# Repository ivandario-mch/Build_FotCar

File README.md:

# Build_FotCar
Construcción del carrito

Carpetas:

Robotica 
--+
  |
  |
  +--CodigosArduino
  |
  |
  |
  +-- Hullas Circuitos
  |
  |
  |
  |
  +-- Diseños 3D

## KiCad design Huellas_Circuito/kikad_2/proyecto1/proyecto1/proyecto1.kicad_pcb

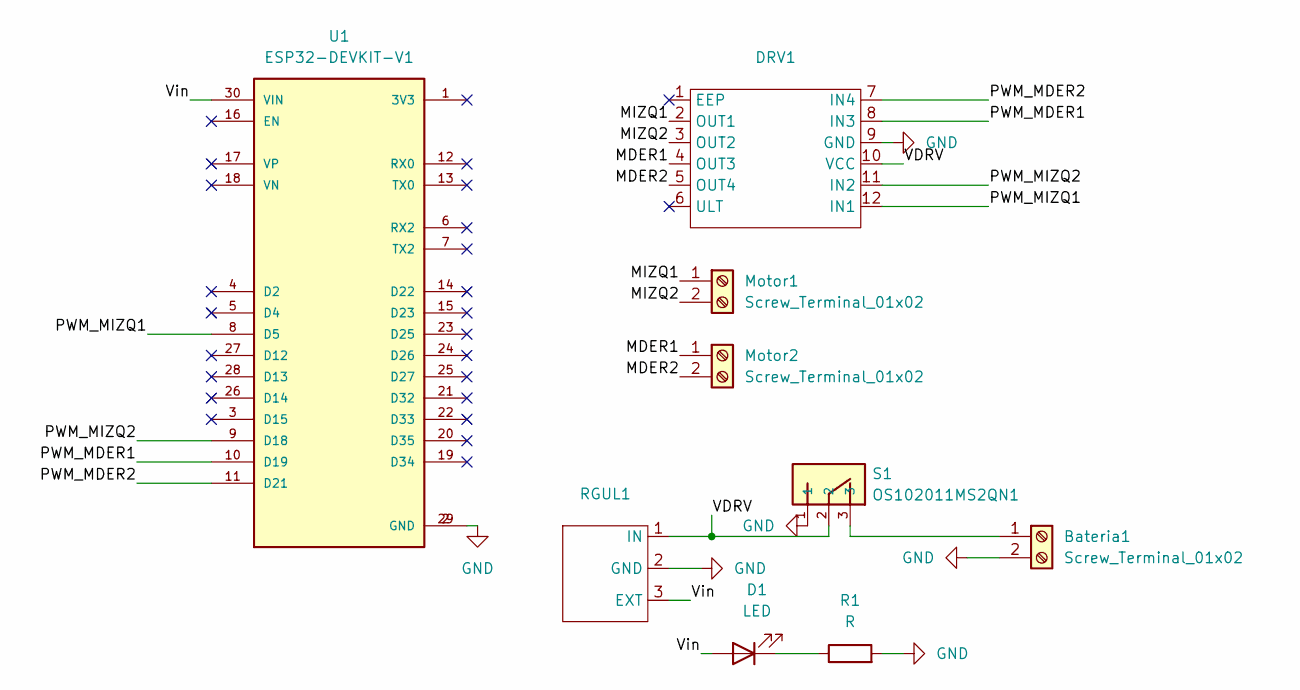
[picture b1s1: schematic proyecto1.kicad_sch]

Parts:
Bateria1: Screw_Terminal_01x02; Molex_KK-254_AE-6410-02A_1x02_P2.54mm_Vertical
D1: LED; LED_D3.0mm
DRV1: DRV_8833
Motor1, Motor2: Screw_Terminal_01x02; Molex_KK-254_AE-6410-02A_1x02_P2.54mm_Vertical
R1: R; R_Axial_DIN0207_L6.3mm_D2.5mm_P7.62mm_Horizontal
RGUL1: RGUL1
S1: OS102011MS2QN1; SW_OS102011MS2QN1
U1: ESP32-DEVKIT-V1; MODULE_ESP32_DEVKIT_V1; PARTREV N/A

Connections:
/MDER1: DRV1.4 (OUT3), Motor2.1
/MDER2: DRV1.5 (OUT4), Motor2.2
/MIZQ1: DRV1.2 (OUT1), Motor1.1
/MIZQ2: DRV1.3 (OUT2), Motor1.2
/PWM_MDER1: DRV1.8 (IN3), U1.10 (D19)
/PWM_MDER2: DRV1.7 (IN4), U1.11 (D21)
/PWM_MIZQ1: DRV1.12 (IN1), U1.8 (D5)
/PWM_MIZQ2: DRV1.11 (IN2), U1.9 (D18)
/VDRV: DRV1.10 (VCC), RGUL1.1 (IN), S1.2
/Vin: D1.2 (A), RGUL1.3 (EXT), U1.30 (VIN)
GND: Bateria1.2, DRV1.9 (GND), R1.2, RGUL1.2 (GND), S1.1, U1.2 (GND), U1.29 (GND)
unnamed: Bateria1.1, S1.3
unnamed: D1.1 (K), R1.1

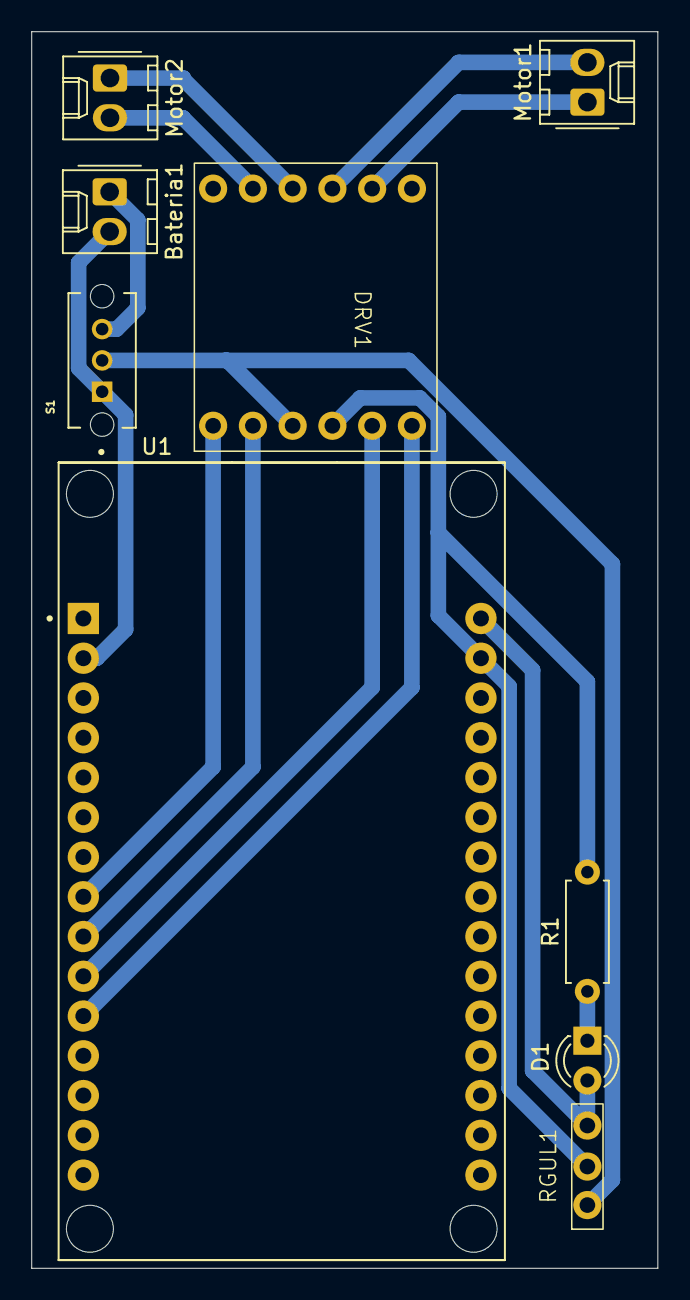
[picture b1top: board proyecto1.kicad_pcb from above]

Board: 2 copper layers, 40.0 x 79.0 mm, 9 parts (0 on the bottom side), 13 nets.

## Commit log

2025-04-09 Demo carrito v-1.0
2025-04-10 readem carpetas
2025-04-10 Prueba1S
2025-04-11 prueba commit
2025-04-19 Creacion_Footprint_Regul&Conectado
2025-04-27 Actualizacion Huellas DRV (NotDefinitive)
2025-05-28 Actualizacion Huellas DRV (NotDefinitive) V2
2025-05-28 Actualizacion Huellas DRV (NotDefinitive) V2.2
